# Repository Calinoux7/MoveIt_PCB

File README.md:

MOTION GAME CONTROLLER – MOVEIT 

MoveIt is a portable game controller that responds to the player’s movements.
During gameplay, the OLED screen randomly displays one of five commands: Up, Down, Left, Right, or Button. It also displays the current score and the high score.

The player must point the controller in the requested direction or press the button when the “Button” command appears. The controller’s movements are detected by the MPU-6050 sensor, which includes an accelerometer and a gyroscope.

An audio system is also built into the controller. A timer sound accompanies the game to indicate the time available to perform the actions. If the player fails to correctly follow a command within the allotted time, the game ends and a defeat sound is played.

To make the game fully portable, the board is powered by three AAA batteries located on the back of the PCB. The PCB was also designed to resemble a retro video game controller.

- How the Game Works 

1. The player presses the START button to begin a new game.
2. The OLED screen displays an initial instruction: Up, Down, Left, Right, or Button.
3. The player must perform the requested action within the allotted time:
   - movements are detected by the MPU-6050;
   - the “Button” action is detected by the dedicated button.
4. If the action is performed correctly and on time, the player earns 1 point and a new instruction appears.
5. The current score and the high score are displayed on the OLED screen during the game.
6. A timer sound plays during the game. If the player fails or runs out of time, the game ends and a failure sound plays.

- Electronic Architecture / Components 

- XIAO ESP32-S3: main microcontroller responsible for managing the game and various peripherals.
- MPU-6050: accelerometer and gyroscope used to detect the controller’s orientation and movements.
- I²C OLED display: shows instructions, the current score, and the high score.
- MAX98357A + Speaker: audio system that plays the timer sound and the defeat sound.
- RGB LED: Provides visual feedback to the player.
- 3 × AAA batteries + AP2112K-3.3: Portable power supply regulated to 3.3 V.
- 3 thermistors: Monitor the temperature of the three batteries.
- START button: Starts a new game.
- Action button: Used when the “Button” instruction appears.

- Circuit Diagram 

The MoveIt circuit diagram includes the various subsystems required for the controller to function: power supply, microcontroller, motion detection, display, user interface, and audio system. The XIAO ESP32-S3 serves as the heart of the system and handles communication with the various components. In particular, the MPU-6050 and the OLED display communicate with the microcontroller via the I²C bus.

The schematic has been organized into different functional blocks to make it easier to read.

- PCB Design 

The PCB was designed entirely in KiCad 10.0. Its shape was inspired by a retro video game controller so that the printed circuit board would be an integral part of the product’s design.
The components were placed with their function and intended use in mind. In particular, the display, buttons, and RGB LED are positioned to be accessible or visible to the player.
The battery holder containing the three AAA batteries is located on the back of the PCB to leave enough space on the front for the electronic components and the user interface.

The routing uses both copper layers of the PCB (F.Cu and B.Cu) to connect the various components.

- Project Files 

    MoveIt_PCB/
    │
    ├── MoveIt_PCB_BELLAICHE Chloé.kicad_pro
    ├── MoveIt_PCB_BELLAICHE Chloé.kicad_sch
    ├── MoveIt_PCB_BELLAICHE Chloé.kicad_pcb
    ├── README_MoveIt.md
    │
    └── images/
        ├── schematic.png
        ├── pcb.png
        ├── pcb_3D_front.png
        └── pcb_3D_back.png

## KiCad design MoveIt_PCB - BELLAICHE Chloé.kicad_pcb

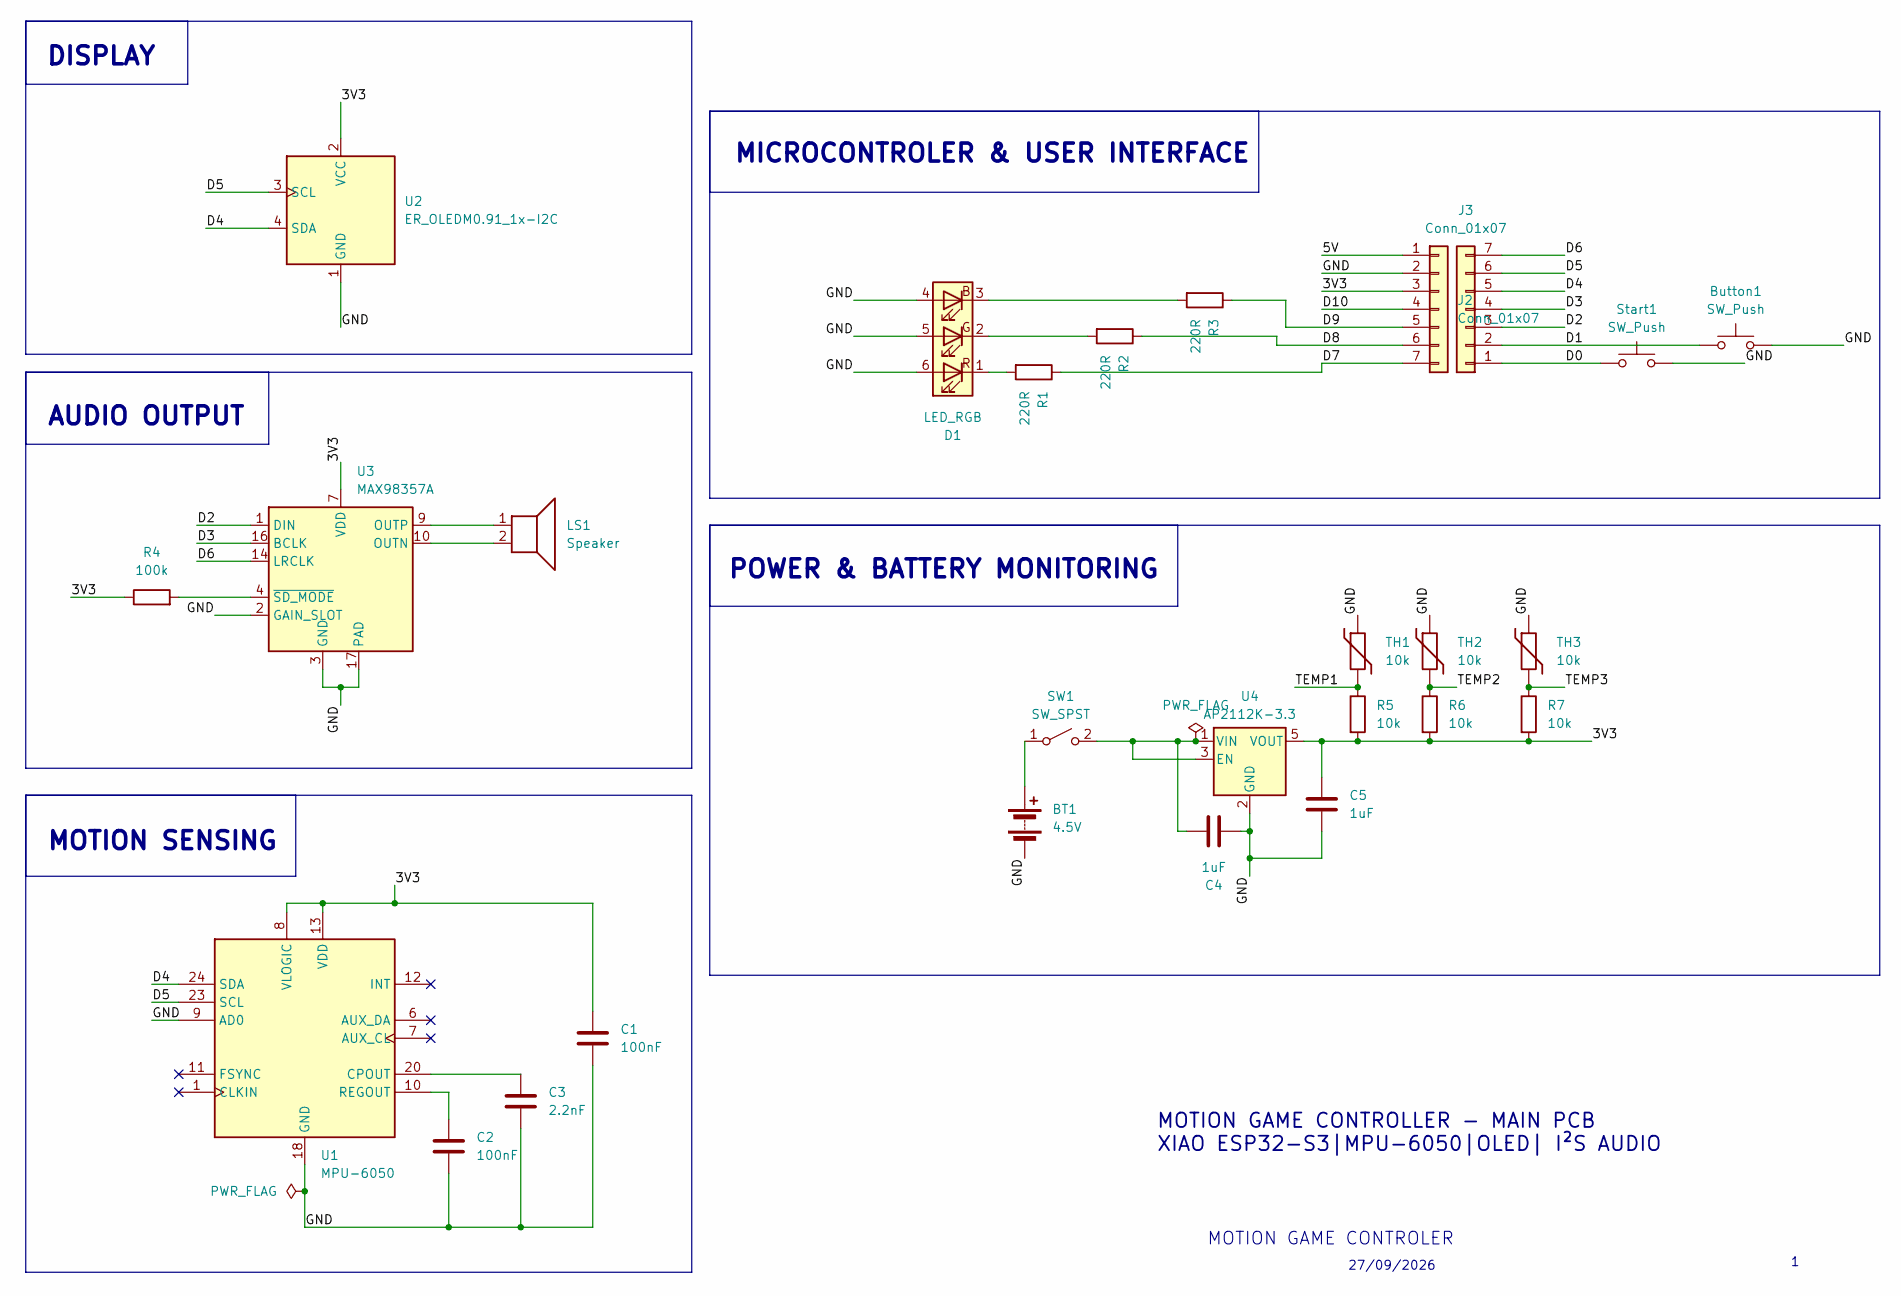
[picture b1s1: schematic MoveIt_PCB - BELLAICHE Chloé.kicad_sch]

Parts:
BT1: 4.5V; BatteryHolder_Keystone_2479_3xAAA
Button1: SW_Push; SW_PUSH_6mm
C1, C2: 100nF; C_Disc_D5.0mm_W2.5mm_P5.00mm
C3: 2.2nF; C_Disc_D5.0mm_W2.5mm_P5.00mm
C4, C5: 1uF; C_Disc_D5.0mm_W2.5mm_P5.00mm
D1: LED_RGB; LED_RGB_5050-6
J2, J3: Conn_01x07; PinHeader_1x07_P2.54mm_Vertical
LS1: Speaker; PinHeader_1x02_P2.54mm_Vertical
R1, R2, R3: 220R; R_Axial_DIN0207_L6.3mm_D2.5mm_P10.16mm_Horizontal
R4: 100k; R_Axial_DIN0207_L6.3mm_D2.5mm_P10.16mm_Horizontal
R5, R6, R7: 10k; R_Axial_DIN0207_L6.3mm_D2.5mm_P10.16mm_Horizontal
SW1: SW_SPST; PinHeader_1x02_P2.54mm_Vertical
Start1: SW_Push; SW_PUSH_6mm
TH1, TH2, TH3: 10k; PinHeader_1x02_P2.54mm_Vertical
U1: MPU-6050; InvenSense_QFN-24_4x4mm_P0.5mm
U2: ER_OLEDM0.91_1x-I2C
U3: MAX98357A; TQFN-16-1EP_3x3mm_P0.5mm_EP1.23x1.23mm
U4: AP2112K-3.3; SOT-23-5

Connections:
/3V3: C1.1, C5.1, J2.3, R4.1, R5.2, R6.2, R7.2, U1.8 (VLOGIC), U1.13 (VDD), U2.2 (VCC), U3.7 (VDD), U3.8 (VDD), U4.5 (VOUT)
/5V: J2.1
/D0: J3.1, Start1.1
/D1: Button1.1, J3.2
/D2: J3.3, U3.1 (DIN)
/D3: J3.4, U3.16 (BCLK)
/D4: J3.5, U1.24 (SDA), U2.4 (SDA)
/D5: J3.6, U1.23 (SCL), U2.3 (SCL)
/D6: J3.7, U3.14 (LRCLK)
/D7: J2.7, R1.1
/D8: J2.6, R2.1
/D9: J2.5, R3.1
/D10: J2.4
/GND: BT1.2 (-), Button1.2, C1.2, C2.2, C3.2, C4.1, C5.2, D1.4 (BA), D1.5 (GA), D1.6 (RA), J2.2, Start1.2, TH1.1, TH2.1, TH3.1, U1.9 (AD0), U1.18 (GND), U2.1 (GND), U3.2 (GAIN_SLOT), U3.3 (GND), U3.11 (GND), U3.15 (GND), U3.17 (PAD), U4.2 (GND)
/TEMP1: R5.1, TH1.2
/TEMP2: R6.1, TH2.2
/TEMP3: R7.1, TH3.2
unnamed: BT1.1 (+), SW1.1 (A)
unnamed: D1.3 (BK), R3.2
unnamed: D1.2 (GK), R2.2
unnamed: D1.1 (RK), R1.2
unnamed: C4.2, SW1.2 (B), U4.1 (VIN), U4.3 (EN)
unnamed: C3.1, U1.20 (CPOUT)
unnamed: C2.1, U1.10 (REGOUT)
unnamed: LS1.2, U3.10 (OUTN)
unnamed: LS1.1, U3.9 (OUTP)
unnamed: R4.2, U3.4 (~SD_MODE)

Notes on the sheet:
AUDIO OUTPUT
POWER & BATTERY MONITORING
MOTION GAME CONTROLLER - MAIN PCB XIAO ESP32-S3|MPU-6050|OLED| I²S AUDIO
MOTION GAME CONTROLER
27/09/2026
DISPLAY
MOTION SENSING
MICROCONTROLER & USER INTERFACE

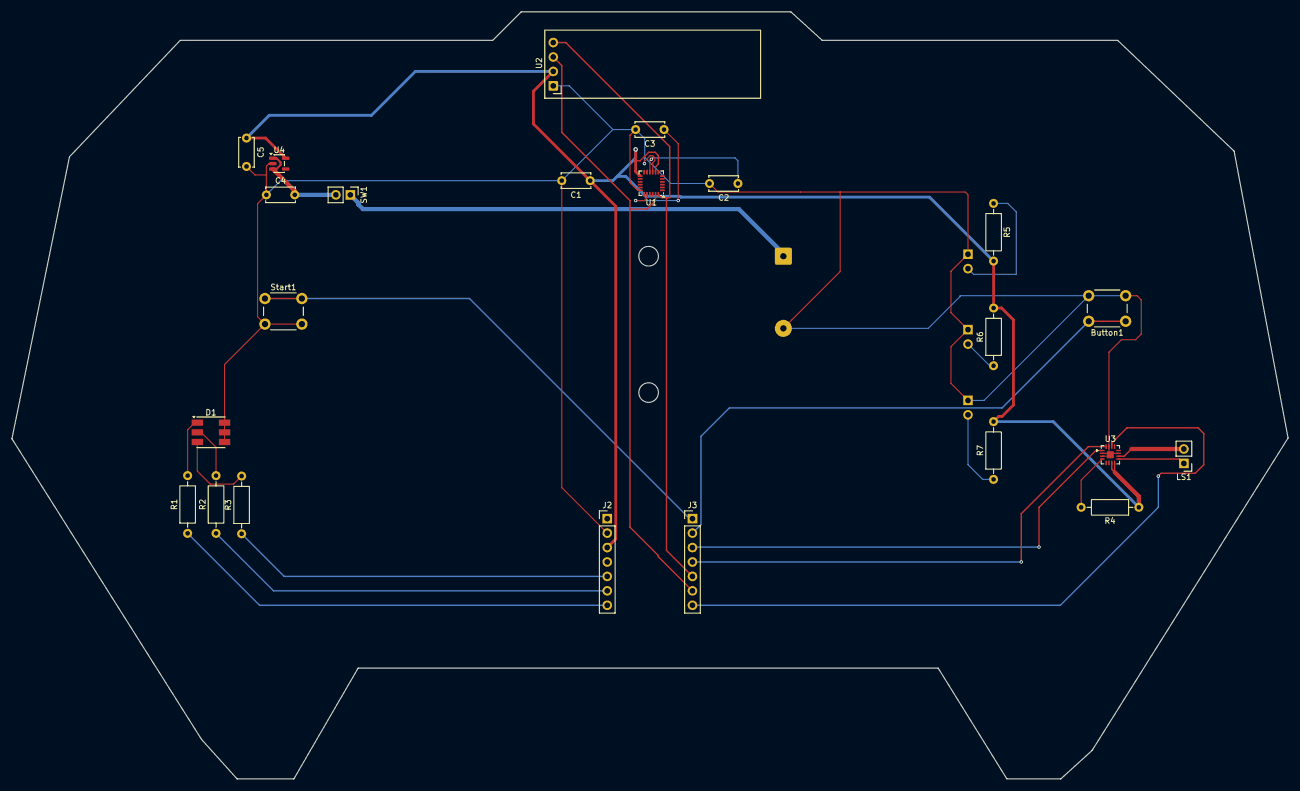
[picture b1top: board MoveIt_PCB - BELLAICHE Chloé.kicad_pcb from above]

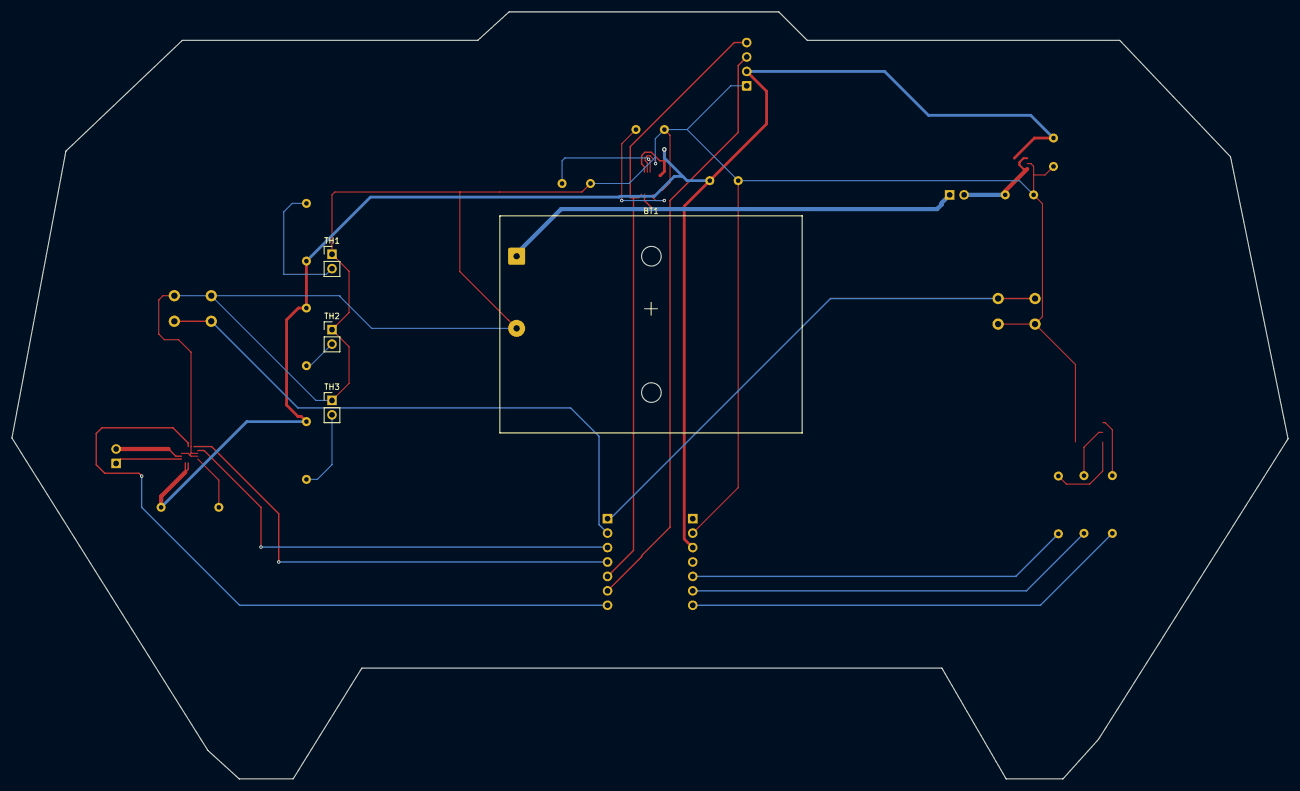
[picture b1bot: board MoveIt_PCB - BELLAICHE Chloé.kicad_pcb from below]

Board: 2 copper layers, 224.6 x 135.0 mm, 27 parts (4 on the bottom side), 25 nets.
